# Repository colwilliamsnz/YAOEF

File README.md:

# YAOEF (Yet Another Open ESP Flasher)

## Status:

Tested. A PCB with this design has been built and tested.

## Introduction:

My remix of a simple "dongle" for flashing ESP32 based devices that have the ESPFlash header implemented (per Jon Oxer, SuperHouse. Ref http://superhouse.tv/espflash).

Why build USB capabilities into every ESP32 design when a simple header will suffice? Save on parts count, footprint, BOM, etc. The dongle supports auto-programming logic and a power switch allows it to be used for serial debugging when under circuit power (I.e., turn the switch off to disable USB power to ESPFlash header).

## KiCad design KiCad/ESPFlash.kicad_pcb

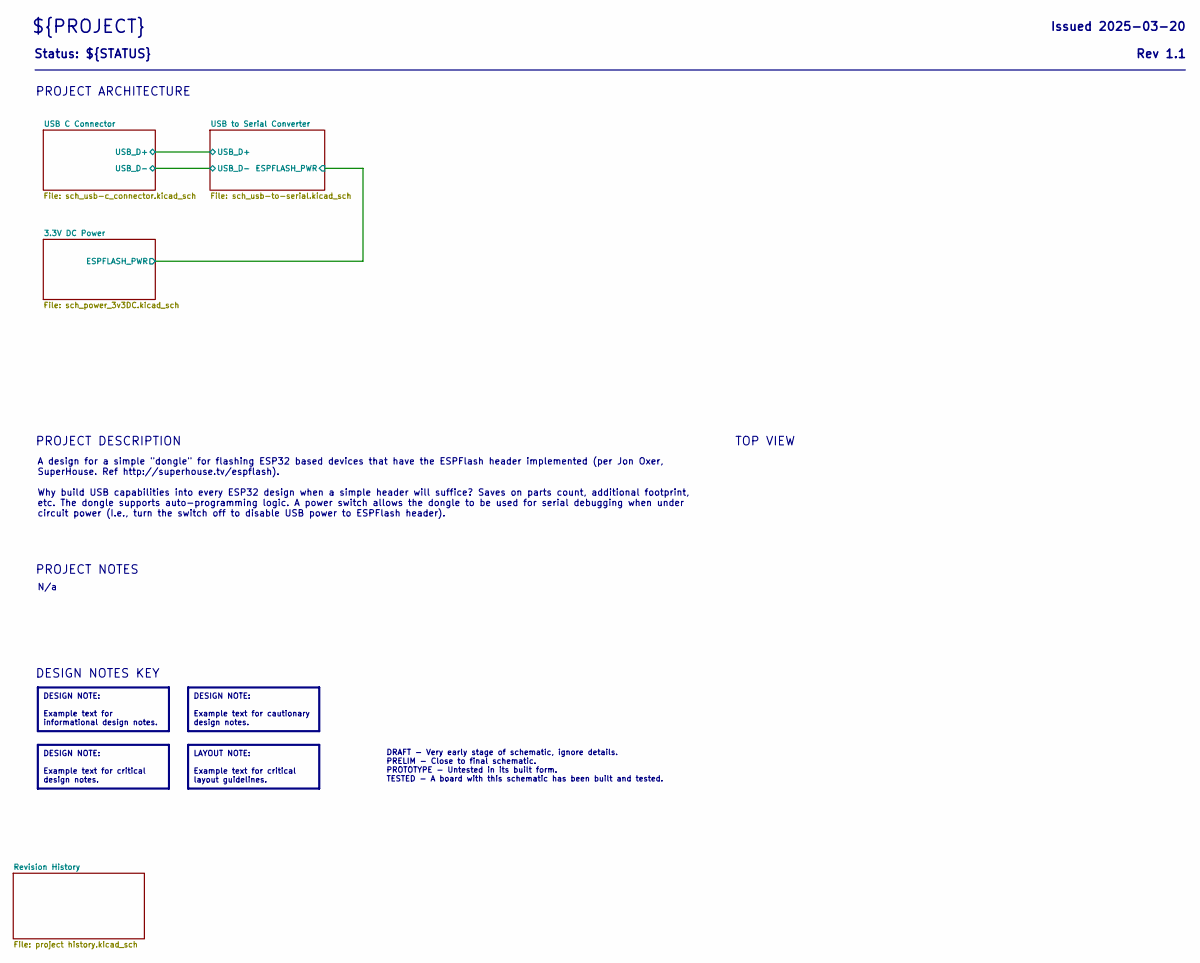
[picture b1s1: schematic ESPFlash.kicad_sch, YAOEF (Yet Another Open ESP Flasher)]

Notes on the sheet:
PROJECT DESCRIPTION
PROJECT NOTES
TOP VIEW
DESIGN NOTES KEY
PROJECT ARCHITECTURE
DESIGN NOTE: Example text for critical design notes.
DESIGN NOTE: Example text for informational design notes.
DESIGN NOTE: Example text for cautionary design notes.
Status: ${STATUS}
DRAFT - Very early stage of schematic, ignore details. PRELIM - Close to final schematic. PROTOTYPE - Untested in its built form. TESTED - A board with this schematic has been built and tested.
N/a
Rev ${REVISION}
A design for a simple "dongle" for flashing ESP32 based devices that have the ESPFlash header implemented (per Jon Oxer, SuperHouse. Ref http://superhouse.tv/espflash). Why build USB capabilities into every ESP32 design when a simple header will suffice? Saves on parts count, additional footprint, 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
${PROJECT}
LAYOUT NOTE: Example text for critical layout guidelines.
Issued ${ISSUE_DATE}

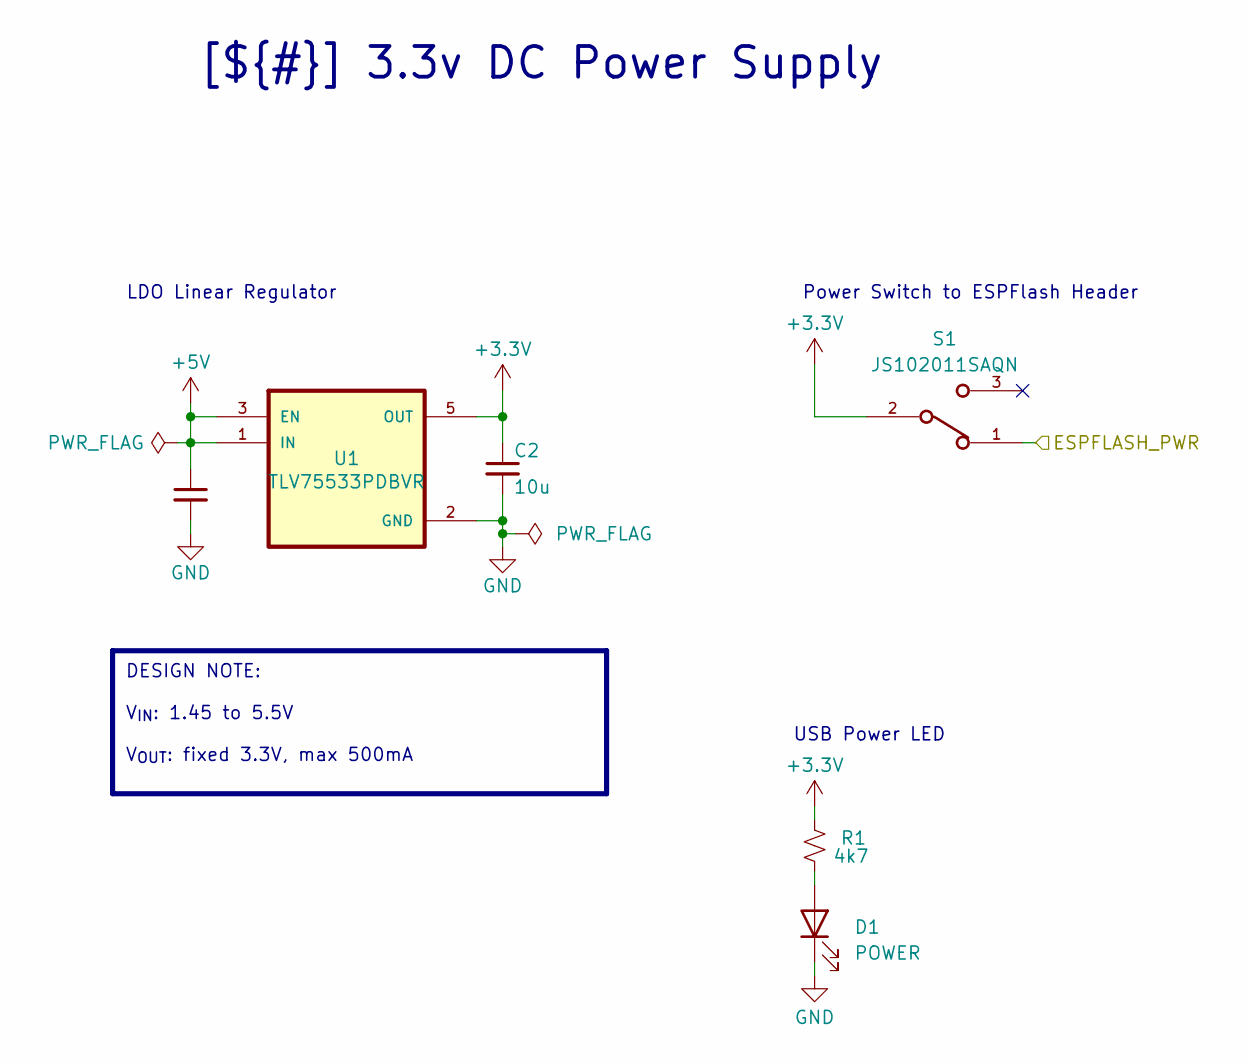
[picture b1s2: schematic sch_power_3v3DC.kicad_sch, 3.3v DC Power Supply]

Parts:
C1, C2: 10u; C_0805_2012Metric; Digikey_PN 490-6473-1-ND
D1: POWER; LED_0603_1608Metric; Digikey_PN 732-4978-1-ND
R1: 4k7; R_0603_1608Metric; Digikey_PN 541-3993-1-ND
S1: JS102011SAQN; SW_JS102011SAQN; Digikey_PN 401-1999-1-ND
U1: TLV75533PDBVR; Digikey_PN 296-50411-1-ND

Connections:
+3.3V: C2.1, R1.2, S1.2, U1.5 (OUT); also elsewhere on the board
+5V: C1.1, U1.1 (IN), U1.3 (EN); also elsewhere on the board
/3.3V DC Power/ESPFLASH_PWR: S1.1; also elsewhere on the board
GND: C1.2, C2.2, D1.1 (K), U1.2 (GND); also elsewhere on the board
unnamed: D1.2 (A), R1.1

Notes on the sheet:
Power Switch to ESPFlash Header
LDO Linear Regulator
USB Power LED
DESIGN NOTE: V_{IN}: 1.45 to 5.5V V_{OUT}: fixed 3.3V, max 500mA
[${#}] ${TITLE}

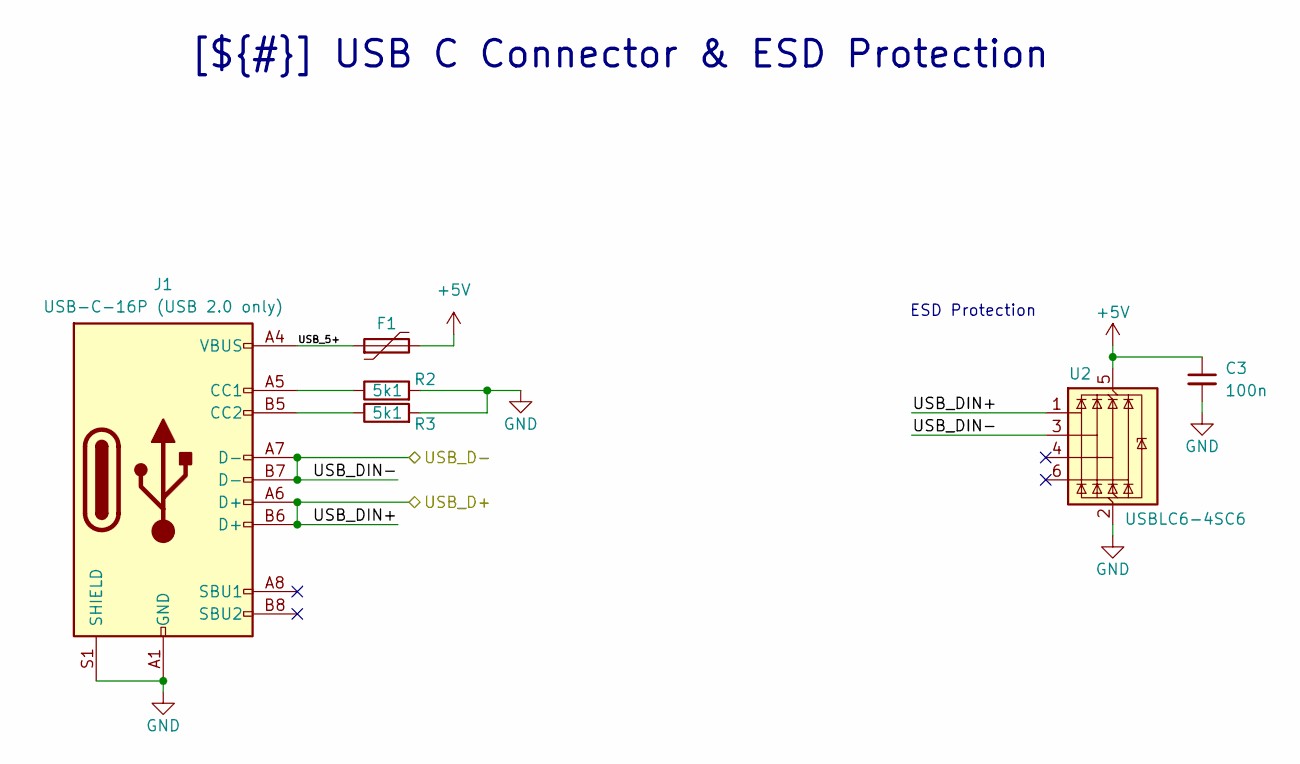
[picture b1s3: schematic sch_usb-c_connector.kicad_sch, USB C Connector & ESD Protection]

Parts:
C3: 100n; C_0603_1608Metric; Digikey_PN 399-C0603C104K4RACTUCT-ND
F1: 6V 500mA; Fuse_0805_2012Metric; Digikey_PN 5923-0ZCK0050FF2ECT-ND
J1: USB-C-16P (USB 2.0 only); GCT_USB4105-GF-A-120; Digikey_PN 2073-USB4105-GF-A-120CT-ND
R2, R3: 5k1; R_0603_1608Metric; Digikey_PN 541-4030-1-ND
U2: USBLC6-4SC6; SOT-23-6; Digikey_PN 497-4492-1-ND

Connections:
+5V: C3.1, F1.2, U2.5 (VBUS); also elsewhere on the board
/USB C Connector/USB_5+: F1.1, J1.A4 (VBUS), J1.A9 (VBUS), J1.B4 (VBUS), J1.B9 (VBUS)
/USB C Connector/USB_DIN+: J1.A6 (D+), J1.B6 (D+), U2.1 (I/O1); also elsewhere on the board
/USB C Connector/USB_DIN-: J1.A7 (D-), J1.B7 (D-), U2.3 (I/O2); also elsewhere on the board
GND: C3.2, J1.A1 (GND), J1.A12 (GND), J1.B1 (GND), J1.B12 (GND), J1.S1 (SHIELD), R2.2, R3.2, U2.2 (GND); also elsewhere on the board
unnamed: J1.A5 (CC1), R2.1
unnamed: J1.B5 (CC2), R3.1

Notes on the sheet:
ESD Protection
[${#}] ${TITLE}

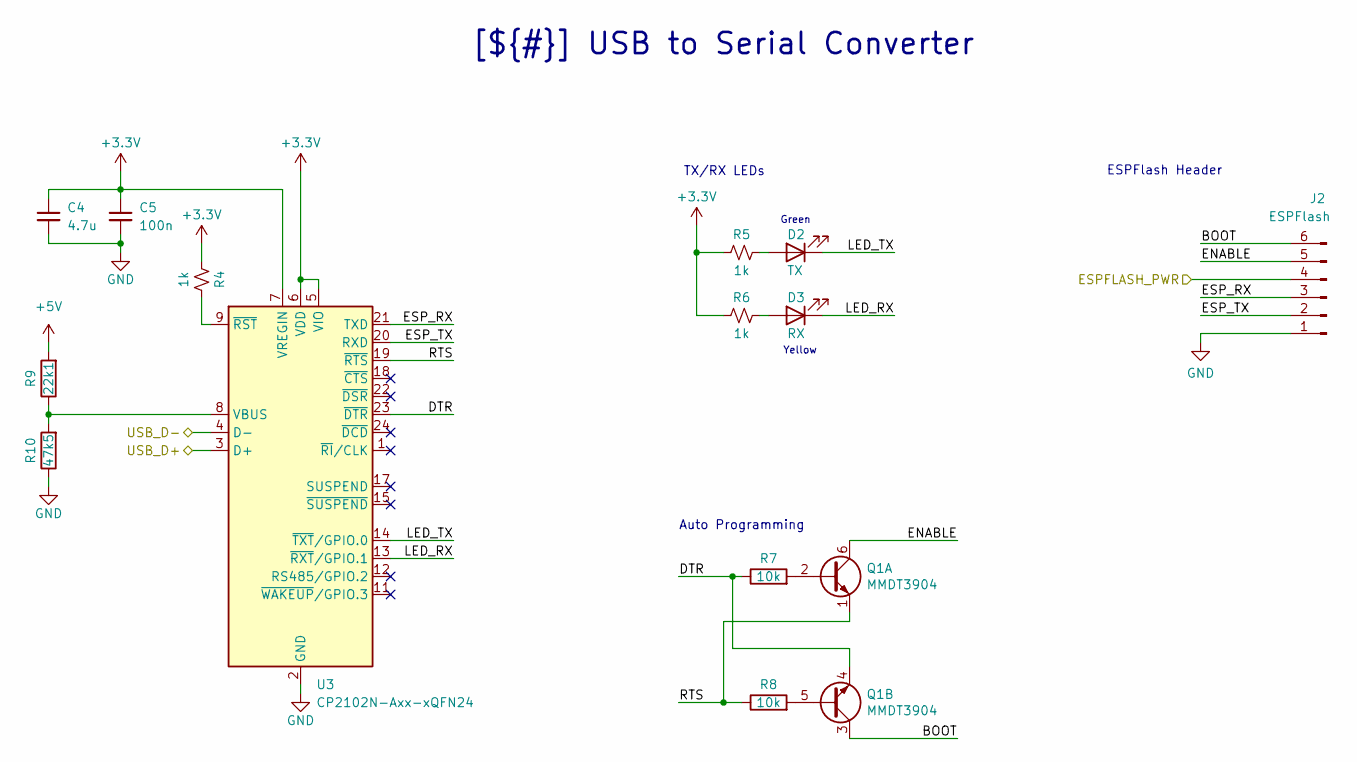
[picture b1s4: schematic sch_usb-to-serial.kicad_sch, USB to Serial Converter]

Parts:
C4: 4.7u; C_0603_1608Metric; Digikey_PN 1276-1784-1-ND
C5: 100n; C_0603_1608Metric; Digikey_PN 399-C0603C104K4RACTUCT-ND
D2: TX; LED_0603_1608Metric; Digikey_PN 732-4980-1-ND
D3: RX; LED_0603_1608Metric; Digikey_PN 160-1434-1-ND
J2: ESPFlash; PinHeader_1x06_P2.54mm_Horizontal
Q1: MMDT3904; SOT-363_SC-70-6; Digikey_PN 4786-MMDT3904CT-ND
R4, R5, R6: 1k; R_0603_1608Metric; Digikey_PN MCT0603-1.00K-MFCT-ND
R7, R8: 10k; R_0603_1608Metric; Digikey_PN A121523CT-ND
R9: 22k1; R_0603_1608Metric; Digikey_PN 541-5271-1-ND
R10: 47k5; R_0603_1608Metric; Digikey_PN 541-4050-1-ND
U3: CP2102N-Axx-xQFN24; QFN-24-1EP_4x4mm_P0.5mm_EP2.6x2.6mm; Digikey_PN CP2102N-A02-GQFN24

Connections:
+3.3V: C4.1, C5.1, R4.2, R5.2, R6.2, U3.5 (VIO), U3.6 (VDD), U3.7 (VREGIN); also elsewhere on the board
+5V: R9.2; also elsewhere on the board
/3.3V DC Power/ESPFLASH_PWR: J2.4; also elsewhere on the board
/USB C Connector/USB_DIN+: U3.3 (D+); also elsewhere on the board
/USB C Connector/USB_DIN-: U3.4 (D-); also elsewhere on the board
/USB to Serial Converter/BOOT: J2.6, Q1.3 (C2)
/USB to Serial Converter/DTR: Q1.4 (E2), R7.1, U3.23 (~DTR)
/USB to Serial Converter/ENABLE: J2.5, Q1.6 (C1)
/USB to Serial Converter/ESP_RX: J2.3, U3.21 (TXD)
/USB to Serial Converter/ESP_TX: J2.2, U3.20 (RXD)
/USB to Serial Converter/LED_RX: D3.1 (K), U3.13 (~RXT/GPIO.1)
/USB to Serial Converter/LED_TX: D2.1 (K), U3.14 (~TXT/GPIO.0)
/USB to Serial Converter/RTS: Q1.1 (E1), R8.1, U3.19 (~RTS)
GND: C4.2, C5.2, J2.1, R10.1, U3.2 (GND), U3.25 (GND); also elsewhere on the board
unnamed: D2.2 (A), R5.1
unnamed: D3.2 (A), R6.1
unnamed: Q1.2 (B1), R7.2
unnamed: Q1.5 (B2), R8.2
unnamed: R9.1, R10.2, U3.8 (VBUS)
unnamed: R4.1, U3.9 (~RST)

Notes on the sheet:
TX/RX LEDs
ESPFlash Header
Green
Yellow
Auto Programming
[${#}] ${TITLE}

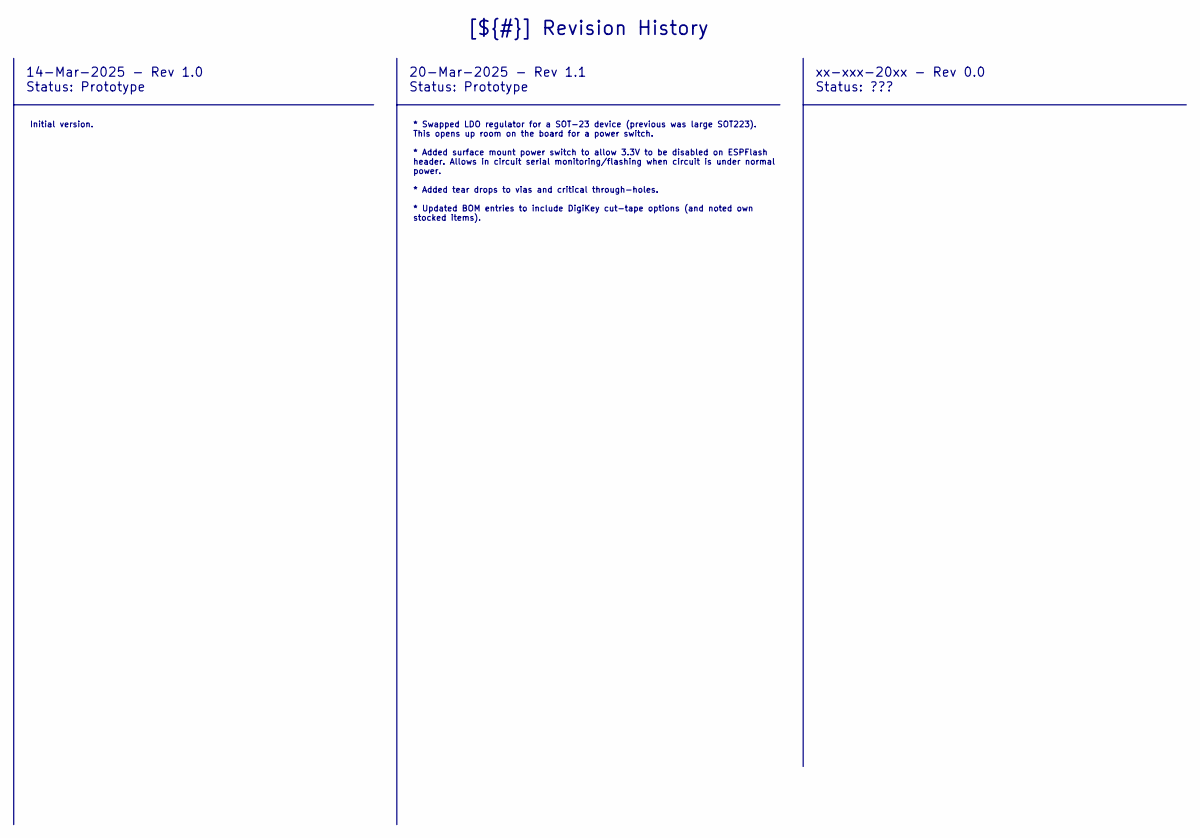
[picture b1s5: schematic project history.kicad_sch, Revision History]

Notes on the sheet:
14-Mar-2025 - Rev 1.0 Status: Prototype
20-Mar-2025 - Rev 1.1 Status: Prototype
xx-xxx-20xx - Rev 0.0 Status: ???
Initial version.
[${#}] ${TITLE}
* Swapped LDO regulator for a SOT-23 device (previous was large SOT223). This opens up room on the board for a power switch. * Added surface mount power switch to allow 3.3V to be disabled on ESPFlash header. Allows in circuit serial monitoring/flashing when circuit is under normal power. * Added t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

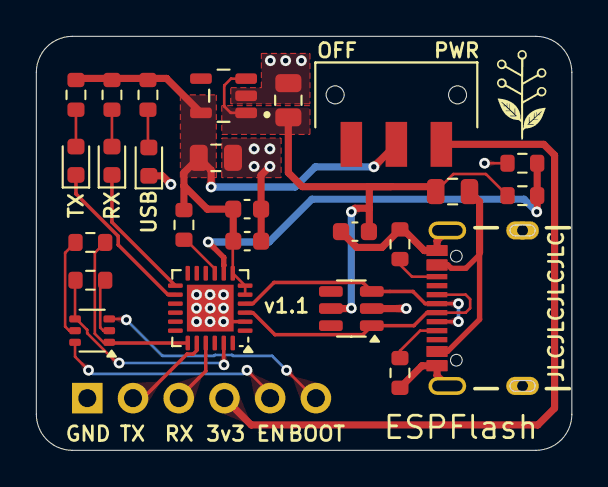
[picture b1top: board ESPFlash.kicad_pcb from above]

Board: 2 copper layers, 29.8 x 23.0 mm, 26 parts (1 on the bottom side), 24 nets.

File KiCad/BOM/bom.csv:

"Reference","Value","Footprint","Qty","Digikey_PN","Stocked"
"C1,C2","10u","Capacitor_SMD:C_0805_2012Metric","2","490-6473-1-ND","Yes"
"C3,C5","100n","Capacitor_SMD:C_0603_1608Metric","2","399-C0603C104K4RACTUCT-ND","Yes"
"C4","4.7u","Capacitor_SMD:C_0603_1608Metric","1","1276-1784-1-ND",""
"D1","POWER","LED_SMD:LED_0603_1608Metric","1","732-4978-1-ND","Yes"
"D2","TX","LED_SMD:LED_0603_1608Metric","1","732-4980-1-ND",""
"D3","RX","LED_SMD:LED_0603_1608Metric","1","160-1434-1-ND",""
"F1","6V 500mA","Fuse:Fuse_0805_2012Metric","1","5923-0ZCK0050FF2ECT-ND",""
"J1","USB-C-16P (USB 2.0 only)","Wattle_Connectors:GCT_USB4105-GF-A-120","1","2073-USB4105-GF-A-120CT-ND",""
"Q1","MMDT3904","Package_TO_SOT_SMD:SOT-363_SC-70-6","1","4786-MMDT3904CT-ND",""
"R1","4k7","Resistor_SMD:R_0603_1608Metric","1","541-3993-1-ND","Yes"
"R2,R3","5k1","Resistor_SMD:R_0603_1608Metric","2","541-4030-1-ND",""
"R4,R5,R6","1k","Resistor_SMD:R_0603_1608Metric","3","MCT0603-1.00K-MFCT-ND","Yes"
"R7,R8","10k","Resistor_SMD:R_0603_1608Metric","2","A121523CT-ND",""
"R9","22k1","Resistor_SMD:R_0603_1608Metric","1","541-5271-1-ND",""
"R10","47k5","Resistor_SMD:R_0603_1608Metric","1","541-4050-1-ND",""
"S1","JS102011SAQN","Wattle_Switches:SW_JS102011SAQN","1","401-1999-1-ND",""
"U1","TLV75533PDBVR","Wattle_Regulators:TLV75533PDBVR","1","296-50411-1-ND",""
"U2","USBLC6-4SC6","Package_TO_SOT_SMD:SOT-23-6","1","497-4492-1-ND",""
"U3","CP2102N-Axx-xQFN24","Package_DFN_QFN:QFN-24-1EP_4x4mm_P0.5mm_EP2.6x2.6mm","1","CP2102N-A02-GQFN24",""

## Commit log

2025-03-20 Initial upload
2025-03-20 Refactor directory structure for entire project
    Move KiCad files to subfolder. Makes Github entry point tidier :)
2025-03-20 Update BoM
    Update components with full description and Digikey P/N.
2025-04-30 Update BOM and general tidy-up
    Include DigiKey cut-tape components and add flag to indicate own stocked items. Remove files that aren't part of the sharable project (KiCad 9 embeds), Remove empty/irrelevant folders.
2025-05-11 Update project status to "Tested".
